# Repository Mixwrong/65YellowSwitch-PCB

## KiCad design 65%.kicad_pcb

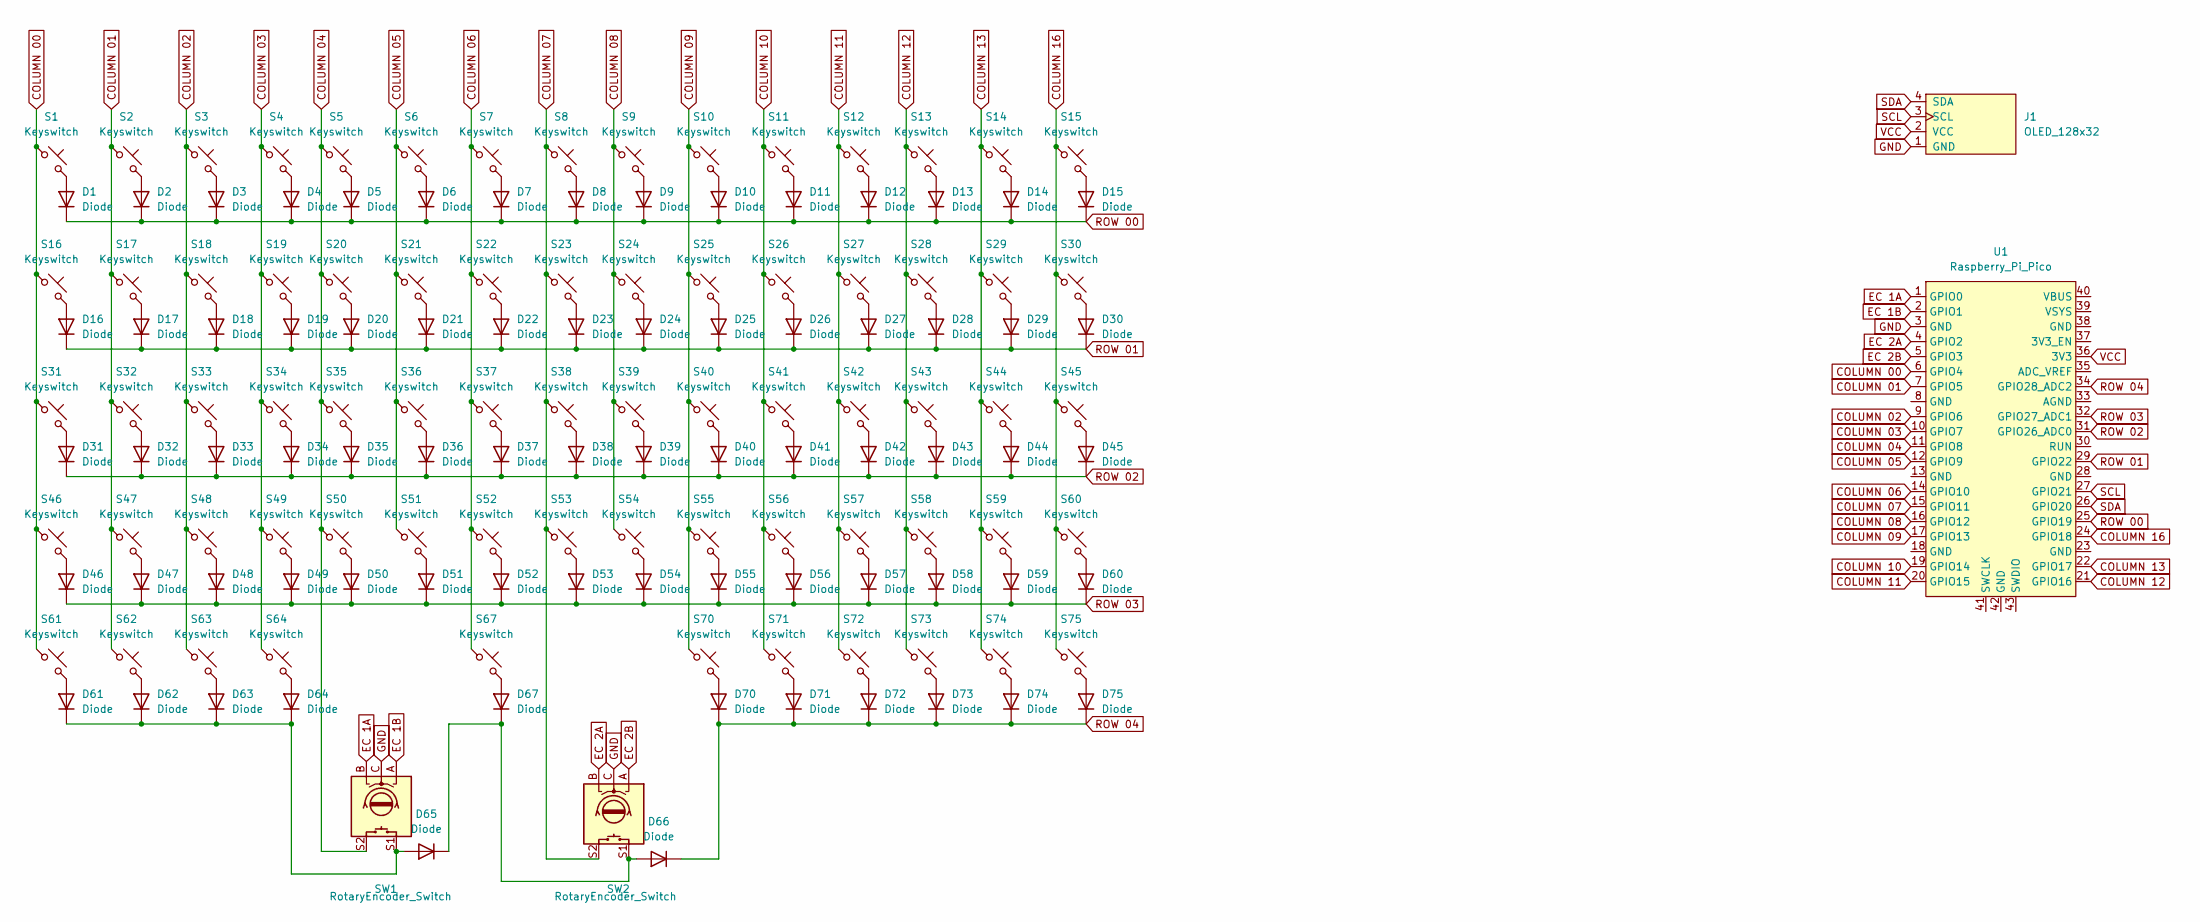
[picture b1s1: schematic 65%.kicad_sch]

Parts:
D1, D2, D3, D4, D5, D6, D7, D8, D9, D10, D11, D12, D13, D14, D15, D16, D17, D18, D19, D20, D21, D22, D23, D24, D25, D26, D27, D28, D29, D30, D31, D32, D33, D34, D35, D36, D37, D38, D39, D40, D41, D42, D43, D44, D45, D46, D47, D48, D49, D50, D51, D52, D53, D54, D55, D56, D57, D58, D59, D60, D61, D62, D63, D64, D65, D66, D67, D70, D71, D72, D73, D74, D75: Diode; Diode_DO-35
J1: OLED_128x32
S1, S2, S3, S4, S5, S6, S7, S8, S9, S10, S11, S12, S13, S15, S17, S18, S19, S20, S21, S22, S23, S24, S25, S26, S27, S28, S30, S31, S33, S34, S35, S36, S37, S38, S39, S40, S41, S42, S43, S45, S46, S48, S49, S50, S51, S52, S53, S54, S55, S56, S57, S59, S60, S61, S70, S71, S72, S73, S74, S75: Keyswitch; Hotswap_MX_1.00u
S14: Keyswitch; Hotswap_MX_2.00u
S16, S29: Keyswitch; Hotswap_MX_1.50u
S32, S58: Keyswitch; Hotswap_MX_1.75u
S44, S47: Keyswitch; Hotswap_MX_2.25u
S62, S63, S64: Keyswitch; Hotswap_MX_1.25u
S67: Keyswitch; Hotswap_MX_6.25u
SW1, SW2: RotaryEncoder_Switch; RotaryEncoder_Alps_EC11E-Switch_Vertical_H20mm
U1: Raspberry_Pi_Pico

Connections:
COLUMN 00: S1.1, S16.1, S31.1, S46.1, S61.1, U1.6 (GPIO4)
COLUMN 01: S2.1, S17.1, S32.1, S47.1, S62.1, U1.7 (GPIO5)
COLUMN 02: S3.1, S18.1, S33.1, S48.1, S63.1, U1.9 (GPIO6)
COLUMN 03: S4.1, S19.1, S34.1, S49.1, S64.1, U1.10 (GPIO7)
COLUMN 04: S5.1, S20.1, S35.1, S50.1, SW1.S2, U1.11 (GPIO8)
COLUMN 05: S6.1, S21.1, S36.1, S51.1, U1.12 (GPIO9)
COLUMN 06: S7.1, S22.1, S37.1, S52.1, S67.1, U1.14 (GPIO10)
COLUMN 07: S8.1, S23.1, S38.1, S53.1, SW2.S2, U1.15 (GPIO11)
COLUMN 08: S9.1, S24.1, S39.1, S54.1, U1.16 (GPIO12)
COLUMN 09: S10.1, S25.1, S40.1, S55.1, S70.1, U1.17 (GPIO13)
COLUMN 10: S11.1, S26.1, S41.1, S56.1, S71.1, U1.19 (GPIO14)
COLUMN 11: S12.1, S27.1, S42.1, S57.1, S72.1, U1.20 (GPIO15)
COLUMN 12: S13.1, S28.1, S43.1, S58.1, S73.1, U1.21 (GPIO16)
COLUMN 13: S14.1, S29.1, S44.1, S59.1, S74.1, U1.22 (GPIO17)
COLUMN 16: S15.1, S30.1, S45.1, S60.1, S75.1, U1.24 (GPIO18)
EC 1A: SW1.B, U1.1 (GPIO0)
EC 1B: SW1.A, U1.2 (GPIO1)
EC 2A: SW2.B, U1.4 (GPIO2)
EC 2B: SW2.A, U1.5 (GPIO3)
GND: J1.1 (GND), SW1.C, SW2.C, U1.3 (GND)
unnamed: D1.2 (A), S1.2
unnamed: D2.2 (A), S2.2
unnamed: D3.2 (A), S3.2
unnamed: D4.2 (A), S4.2
unnamed: D5.2 (A), S5.2
unnamed: D6.2 (A), S6.2
unnamed: D7.2 (A), S7.2
unnamed: D8.2 (A), S8.2
unnamed: D9.2 (A), S9.2
unnamed: D10.2 (A), S10.2
unnamed: D11.2 (A), S11.2
unnamed: D12.2 (A), S12.2
unnamed: D13.2 (A), S13.2
unnamed: D14.2 (A), S14.2
unnamed: D15.2 (A), S15.2
unnamed: D16.2 (A), S16.2
unnamed: D17.2 (A), S17.2
unnamed: D18.2 (A), S18.2
unnamed: D19.2 (A), S19.2
unnamed: D20.2 (A), S20.2
unnamed: D21.2 (A), S21.2
unnamed: D22.2 (A), S22.2
unnamed: D23.2 (A), S23.2
unnamed: D24.2 (A), S24.2
unnamed: D25.2 (A), S25.2
unnamed: D26.2 (A), S26.2
unnamed: D27.2 (A), S27.2
unnamed: D28.2 (A), S28.2
unnamed: D29.2 (A), S29.2
unnamed: D30.2 (A), S30.2
unnamed: D31.2 (A), S31.2
unnamed: D32.2 (A), S32.2
unnamed: D33.2 (A), S33.2
unnamed: D34.2 (A), S34.2
unnamed: D35.2 (A), S35.2
unnamed: D36.2 (A), S36.2
unnamed: D37.2 (A), S37.2
unnamed: D38.2 (A), S38.2
unnamed: D39.2 (A), S39.2
unnamed: D40.2 (A), S40.2
unnamed: D41.2 (A), S41.2
unnamed: D42.2 (A), S42.2
unnamed: D43.2 (A), S43.2
unnamed: D44.2 (A), S44.2
unnamed: D45.2 (A), S45.2
unnamed: D46.2 (A), S46.2
unnamed: D47.2 (A), S47.2
unnamed: D48.2 (A), S48.2
unnamed: D49.2 (A), S49.2
unnamed: D50.2 (A), S50.2
unnamed: D51.2 (A), S51.2
unnamed: D52.2 (A), S52.2
unnamed: D53.2 (A), S53.2
unnamed: D54.2 (A), S54.2
unnamed: D55.2 (A), S55.2
unnamed: D56.2 (A), S56.2
unnamed: D57.2 (A), S57.2
unnamed: D58.2 (A), S58.2
unnamed: D59.2 (A), S59.2
unnamed: D60.2 (A), S60.2
unnamed: D61.2 (A), S61.2
unnamed: D61.1 (K), D62.1 (K), D63.1 (K), D64.1 (K), D65.2 (A), SW1.S1
unnamed: D62.2 (A), S62.2
unnamed: D63.2 (A), S63.2
unnamed: D64.2 (A), S64.2
unnamed: D65.1 (K), D66.2 (A), D67.1 (K), SW2.S1
unnamed: D67.2 (A), S67.2
unnamed: D70.2 (A), S70.2
unnamed: D71.2 (A), S71.2
unnamed: D72.2 (A), S72.2
unnamed: D73.2 (A), S73.2
unnamed: D74.2 (A), S74.2
unnamed: D75.2 (A), S75.2
ROW 00: D1.1 (K), D2.1 (K), D3.1 (K), D4.1 (K), D5.1 (K), D6.1 (K), D7.1 (K), D8.1 (K), D9.1 (K), D10.1 (K), D11.1 (K), D12.1 (K), D13.1 (K), D14.1 (K), D15.1 (K), U1.25 (GPIO19)
ROW 01: D16.1 (K), D17.1 (K), D18.1 (K), D19.1 (K), D20.1 (K), D21.1 (K), D22.1 (K), D23.1 (K), D24.1 (K), D25.1 (K), D26.1 (K), D27.1 (K), D28.1 (K), D29.1 (K), D30.1 (K), U1.29 (GPIO22)
ROW 02: D31.1 (K), D32.1 (K), D33.1 (K), D34.1 (K), D35.1 (K), D36.1 (K), D37.1 (K), D38.1 (K), D39.1 (K), D40.1 (K), D41.1 (K), D42.1 (K), D43.1 (K), D44.1 (K), D45.1 (K), U1.31 (GPIO26_ADC0)
ROW 03: D46.1 (K), D47.1 (K), D48.1 (K), D49.1 (K), D50.1 (K), D51.1 (K), D52.1 (K), D53.1 (K), D54.1 (K), D55.1 (K), D56.1 (K), D57.1 (K), D58.1 (K), D59.1 (K), D60.1 (K), U1.32 (GPIO27_ADC1)
ROW 04: D66.1 (K), D70.1 (K), D71.1 (K), D72.1 (K), D73.1 (K), D74.1 (K), D75.1 (K), U1.34 (GPIO28_ADC2)
SCL: J1.3 (SCL), U1.27 (GPIO21)
SDA: J1.4 (SDA), U1.26 (GPIO20)
VCC: J1.2 (VCC), U1.36 (3V3)

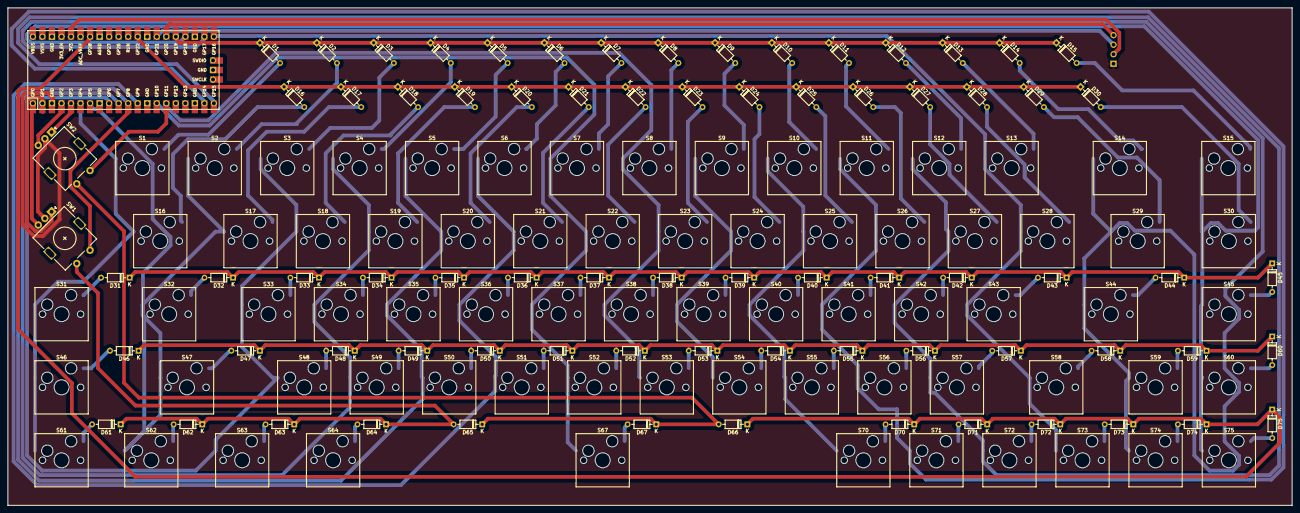
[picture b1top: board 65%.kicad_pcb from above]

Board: 2 copper layers, 342.3 x 132.6 mm, 148 parts (0 on the bottom side), 101 nets.
